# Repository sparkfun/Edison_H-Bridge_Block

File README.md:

Dual H-bridge
=====================

The Dual H-bridge give the Edison some ability to move when paired with two DC motors.  This board can drive two DC motors at voltages ranging from 2.7V-15V and currents up to 1amp.  This board is isolated from the Edison using a logic level converter.  To use this board external power for the motors will be required.  Power for the motors is supplied on the headers labled "VIN" and "GND"

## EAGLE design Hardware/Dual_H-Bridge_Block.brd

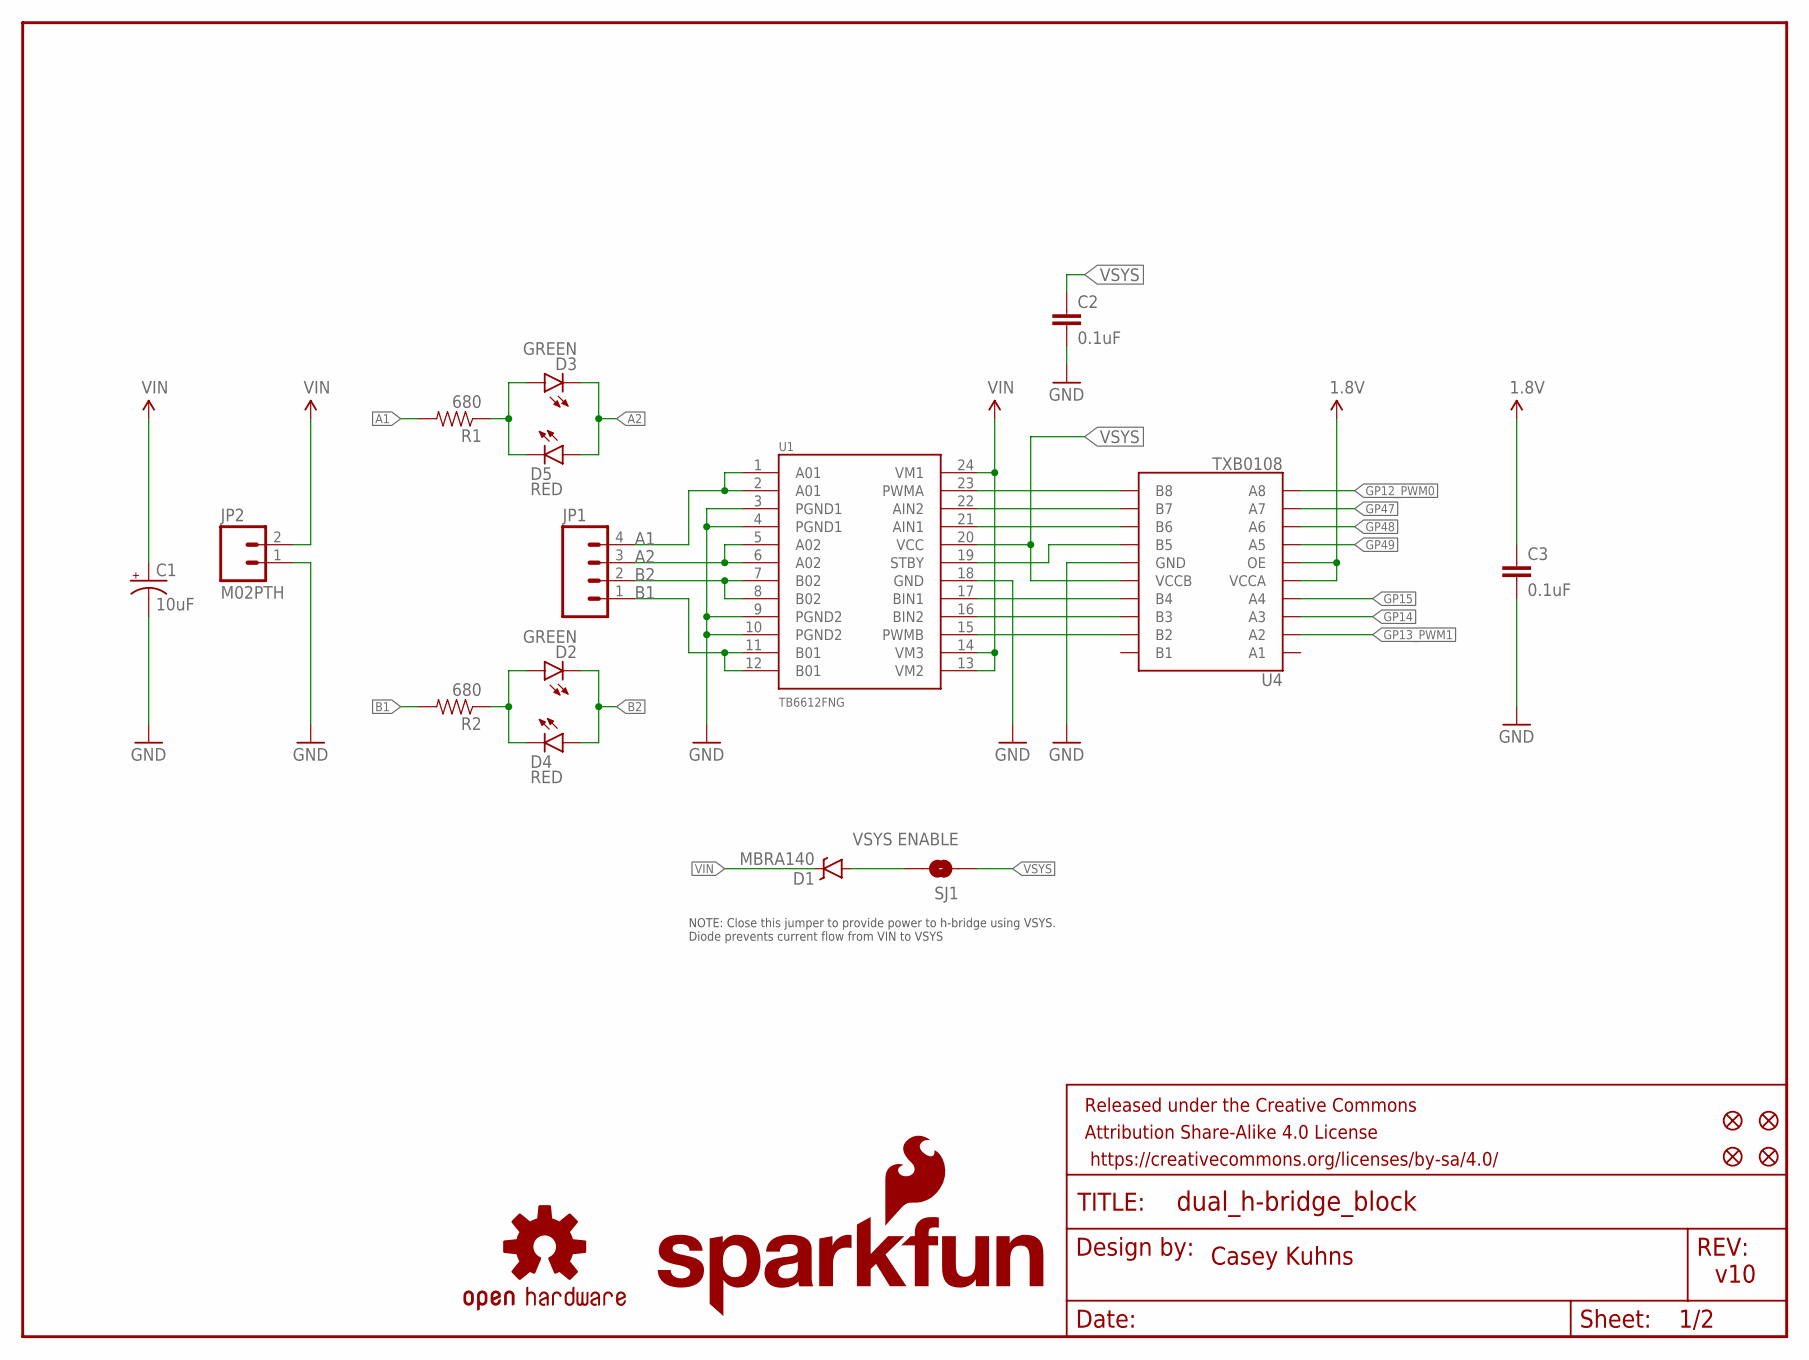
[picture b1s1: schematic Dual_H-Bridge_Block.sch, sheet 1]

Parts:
C1: 10uF; EIA3216
C2, C3: 0.1uF; 0603-CAP
D1: MBRA140; SMA-DIODE
D2, D3: GREEN; LED-0603
D4, D5: RED; LED-0603
FID1, FID2, FID3, FID4: FIDUCIAL1X2; FIDUCIAL-1X2
FRAME1: FRAME-LETTER; CREATIVE_COMMONS
JP1: M04PTH; 1X04
JP2: M02PTH; 1X02
LOGO1: OSHW-LOGOS; OSHW-LOGO-S
LOGO4: SFE_LOGO_NAME_FLAME.1_INCH; SFE_LOGO_NAME_FLAME_.1
R1, R2: 680; 0603-RES
SJ1: VSYS ENABLE; PAD-JUMPER-2-NO_YES_SILK
U1: TB6612FNG; SSOP24
U4: TXB0108; UFDFN-20

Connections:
1.8V: C3.1, U4.5 (VCCA), U4.6 (OE); also elsewhere on the board
A1: JP1.4, R1.2, U1.1 (A01), U1.2 (A01)
A2: D3.C, D5.A, JP1.3, U1.5 (A02), U1.6 (A02)
B1: JP1.1, R2.2, U1.11 (B01), U1.12 (B01)
B2: D2.C, D4.A, JP1.2, U1.7 (B02), U1.8 (B02)
GND: C1.C (-), C2.2, C3.2, JP2.1, U1.3 (PGND1), U1.4 (PGND1), U1.9 (PGND2), U1.10 (PGND2), U1.18 (GND), U4.15 (GND); also elsewhere on the board
GP12_PWM0: U4.10 (A8); also elsewhere on the board
GP13_PWM1: U4.2 (A2); also elsewhere on the board
GP14: U4.3 (A3); also elsewhere on the board
GP15: U4.4 (A4); also elsewhere on the board
GP47: U4.9 (A7); also elsewhere on the board
GP48: U4.8 (A6); also elsewhere on the board
GP49: U4.7 (A5); also elsewhere on the board
unnamed: D1.A, SJ1.2
unnamed: D2.A, D4.C, R2.1
unnamed: U1.15 (PWMB), U4.19 (B2)
unnamed: U1.23 (PWMA), U4.11 (B8)
unnamed: D3.A, D5.C, R1.1
unnamed: U1.19 (STBY), U4.14 (B5)
unnamed: U1.17 (BIN1), U4.17 (B4)
unnamed: U1.16 (BIN2), U4.18 (B3)
unnamed: U1.21 (AIN1), U4.13 (B6)
unnamed: U1.22 (AIN2), U4.12 (B7)
VIN: C1.A (+), D1.C, JP2.2, U1.13 (VM2), U1.14 (VM3), U1.24 (VM1)
VSYS: C2.1, SJ1.1, U1.20 (VCC), U4.16 (VCCB); also elsewhere on the board

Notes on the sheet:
v10
Casey Kuhns
NOTE: Close this jumper to provide power to h-bridge using VSYS. Diode prevents current flow from VIN to VSYS

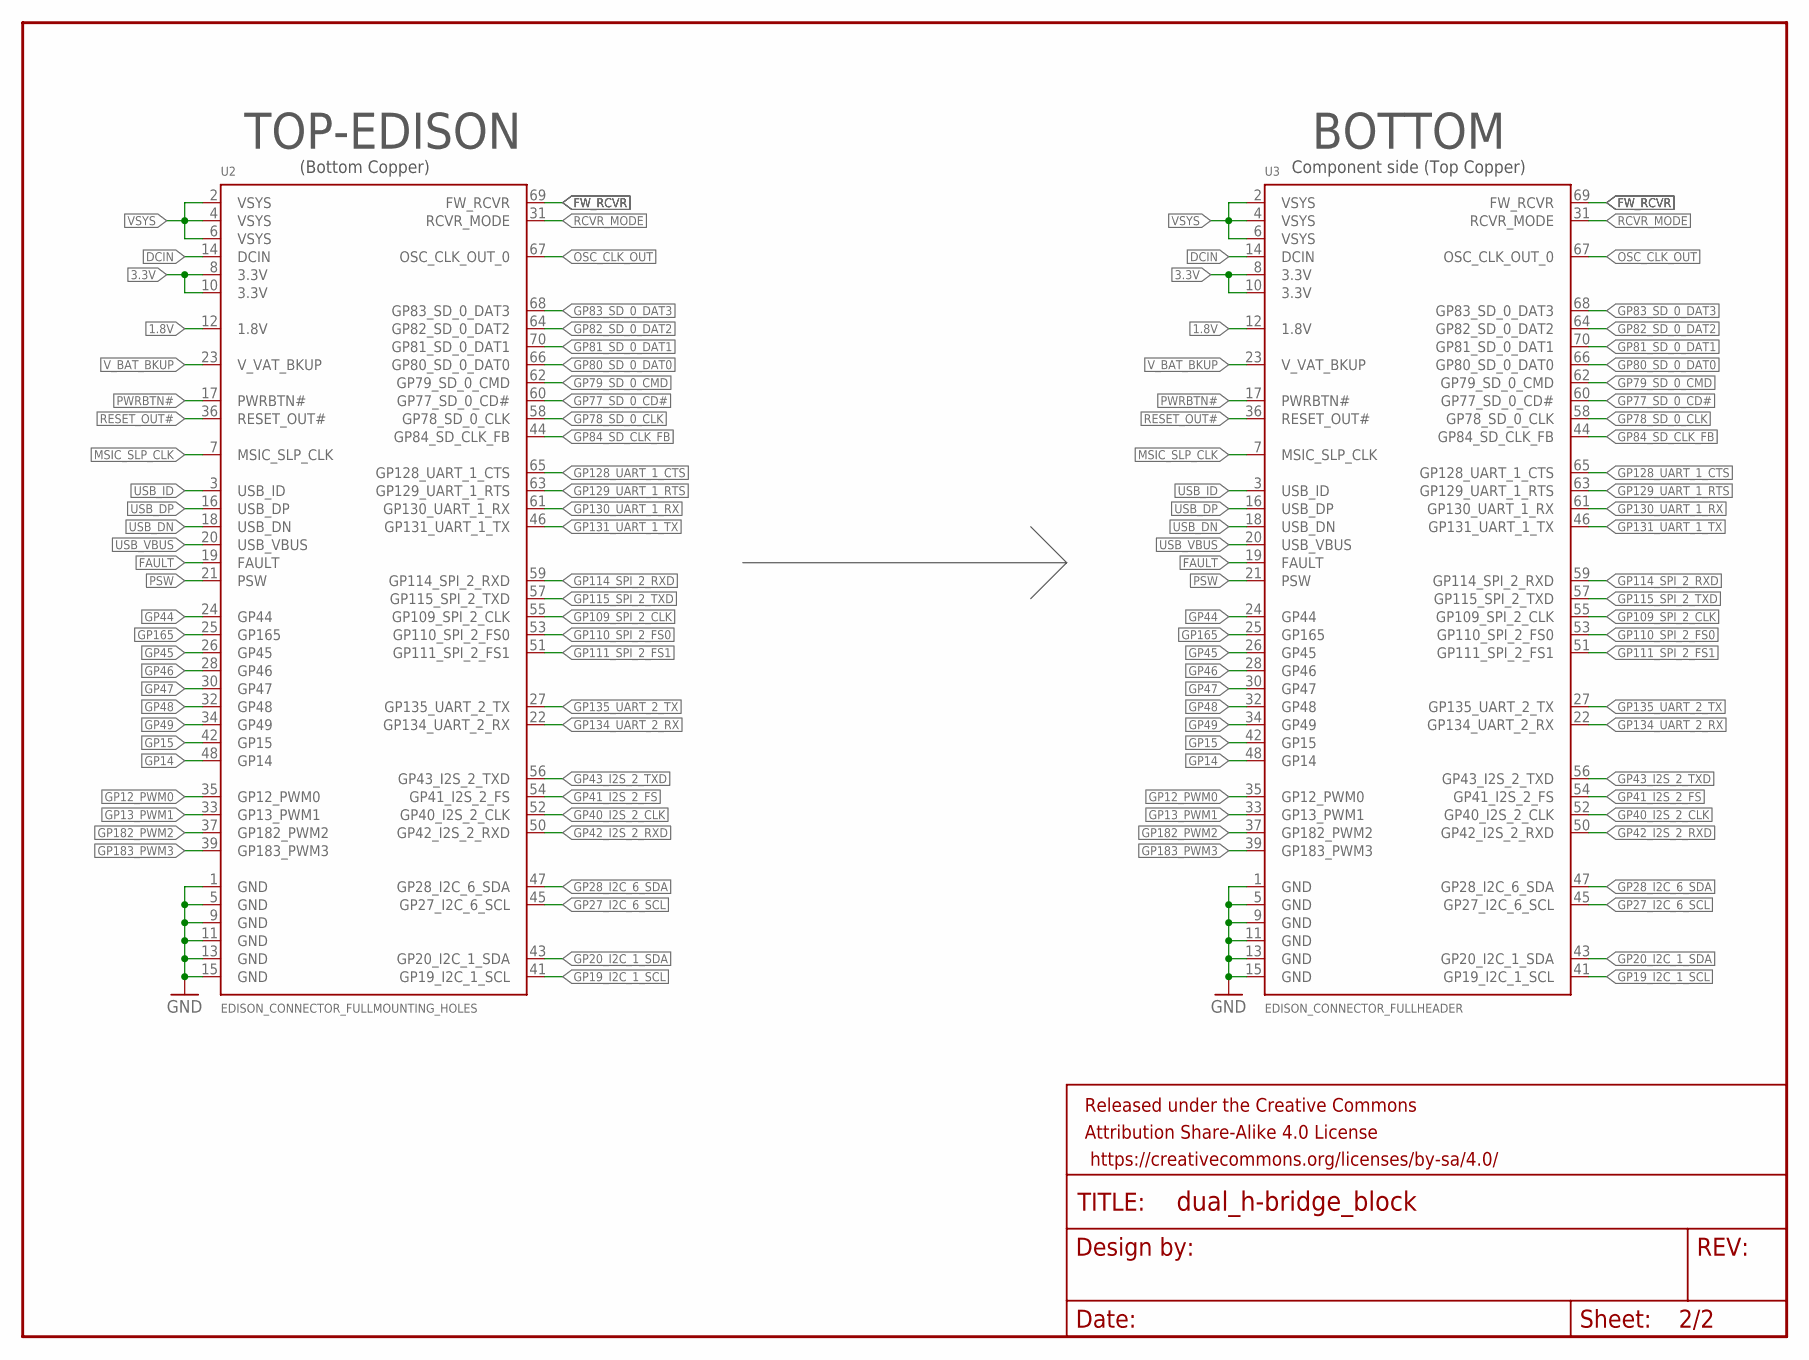
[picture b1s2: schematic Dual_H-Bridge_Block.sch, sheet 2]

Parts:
FRAME2: FRAME-LETTER; CREATIVE_COMMONS
U2: EDISON_CONNECTOR_FULLMOUNTING_HOLES; EDISON_DAUGHTER
U3: EDISON_CONNECTOR_FULLHEADER; DF40C-70DP-0.4(51)

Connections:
1.8V: U2.12 (1.8V), U3.12 (1.8V); also elsewhere on the board
3.3V: U2.8 (3.3V), U2.10 (3.3V), U3.8 (3.3V), U3.10 (3.3V)
DCIN: U2.14 (DCIN), U3.14 (DCIN)
FAULT: U2.19 (FAULT), U3.19 (FAULT)
FW_RCVR: U2.69 (FW_RCVR), U3.69 (FW_RCVR)
GND: U2.1 (GND), U2.5 (GND), U2.9 (GND), U2.11 (GND), U2.13 (GND), U2.15 (GND), U3.1 (GND), U3.5 (GND), U3.9 (GND), U3.11 (GND), U3.13 (GND), U3.15 (GND); also elsewhere on the board
GP12_PWM0: U2.35 (GP12_PWM0), U3.35 (GP12_PWM0); also elsewhere on the board
GP13_PWM1: U2.33 (GP13_PWM1), U3.33 (GP13_PWM1); also elsewhere on the board
GP14: U2.48 (GP14), U3.48 (GP14); also elsewhere on the board
GP15: U2.42 (GP15), U3.42 (GP15); also elsewhere on the board
GP19_I2C_1_SCL: U2.41 (GP19_I2C_1_SCL), U3.41 (GP19_I2C_1_SCL)
GP20_I2C_1_SDA: U2.43 (GP20_I2C_1_SDA), U3.43 (GP20_I2C_1_SDA)
GP27_I2C_6_SCL: U2.45 (GP27_I2C_6_SCL), U3.45 (GP27_I2C_6_SCL)
GP28_I2C_6_SDA: U2.47 (GP28_I2C_6_SDA), U3.47 (GP28_I2C_6_SDA)
GP40_I2S_2_CLK: U2.52 (GP40_I2S_2_CLK), U3.52 (GP40_I2S_2_CLK)
GP41_I2S_2_FS: U2.54 (GP41_I2S_2_FS), U3.54 (GP41_I2S_2_FS)
GP42_I2S_2_RXD: U2.50 (GP42_I2S_2_RXD), U3.50 (GP42_I2S_2_RXD)
GP43_I2S_2_TXD: U2.56 (GP43_I2S_2_TXD), U3.56 (GP43_I2S_2_TXD)
GP44: U2.24 (GP44), U3.24 (GP44)
GP45: U2.26 (GP45), U3.26 (GP45)
GP46: U2.28 (GP46), U3.28 (GP46)
GP47: U2.30 (GP47), U3.30 (GP47); also elsewhere on the board
GP48: U2.32 (GP48), U3.32 (GP48); also elsewhere on the board
GP49: U2.34 (GP49), U3.34 (GP49); also elsewhere on the board
GP77_SD_0_CD#: U2.60 (GP77_SD_0_CD#), U3.60 (GP77_SD_0_CD#)
GP78_SD_0_CLK: U2.58 (GP78_SD_0_CLK), U3.58 (GP78_SD_0_CLK)
GP79_SD_0_CMD: U2.62 (GP79_SD_0_CMD), U3.62 (GP79_SD_0_CMD)
GP80_SD_0_DAT0: U2.66 (GP80_SD_0_DAT0), U3.66 (GP80_SD_0_DAT0)
GP81_SD_0_DAT1: U2.70 (GP81_SD_0_DAT1), U3.70 (GP81_SD_0_DAT1)
GP82_SD_0_DAT2: U2.64 (GP82_SD_0_DAT2), U3.64 (GP82_SD_0_DAT2)
GP83_SD_0_DAT3: U2.68 (GP83_SD_0_DAT3), U3.68 (GP83_SD_0_DAT3)
GP84_SD_CLK_FB: U2.44 (GP84_SD_CLK_FB), U3.44 (GP84_SD_CLK_FB)
GP109_SPI_2_CLK: U2.55 (GP109_SPI_2_CLK), U3.55 (GP109_SPI_2_CLK)
GP110_SPI_2_FS0: U2.53 (GP110_SPI_2_FS0), U3.53 (GP110_SPI_2_FS0)
GP111_SPI_2_FS1: U2.51 (GP111_SPI_2_FS1), U3.51 (GP111_SPI_2_FS1)
GP114_SPI_2_RXD: U2.59 (GP114_SPI_2_RXD), U3.59 (GP114_SPI_2_RXD)
GP115_SPI_2_TXD: U2.57 (GP115_SPI_2_TXD), U3.57 (GP115_SPI_2_TXD)
GP128_UART_1_CTS: U2.65 (GP128_UART_1_CTS), U3.65 (GP128_UART_1_CTS)
GP129_UART_1_RTS: U2.63 (GP129_UART_1_RTS), U3.63 (GP129_UART_1_RTS)
GP130_UART_1_RX: U2.61 (GP130_UART_1_RX), U3.61 (GP130_UART_1_RX)
GP131_UART_1_TX: U2.46 (GP131_UART_1_TX), U3.46 (GP131_UART_1_TX)
GP134_UART_2_RX: U2.22 (GP134_UART_2_RX), U3.22 (GP134_UART_2_RX)
GP135_UART_2_TX: U2.27 (GP135_UART_2_TX), U3.27 (GP135_UART_2_TX)
GP165: U2.25 (GP165), U3.25 (GP165)
GP182_PWM2: U2.37 (GP182_PWM2), U3.37 (GP182_PWM2)
GP183_PWM3: U2.39 (GP183_PWM3), U3.39 (GP183_PWM3)
MSIC_SLP_CLK: U2.7 (MSIC_SLP_CLK), U3.7 (MSIC_SLP_CLK)
OSC_CLK_OUT: U2.67 (OSC_CLK_OUT_0), U3.67 (OSC_CLK_OUT_0)
PSW: U2.21 (PSW), U3.21 (PSW)
PWRBTN#: U2.17 (PWRBTN#), U3.17 (PWRBTN#)
RCVR_MODE: U2.31 (RCVR_MODE), U3.31 (RCVR_MODE)
RESET_OUT#: U2.36 (RESET_OUT#), U3.36 (RESET_OUT#)
USB_DN: U2.18 (USB_DN), U3.18 (USB_DN)
USB_DP: U2.16 (USB_DP), U3.16 (USB_DP)
USB_ID: U2.3 (USB_ID), U3.3 (USB_ID)
USB_VBUS: U2.20 (USB_VBUS), U3.20 (USB_VBUS)
VSYS: U2.2 (VSYS), U2.4 (VSYS), U2.6 (VSYS), U3.2 (VSYS), U3.4 (VSYS), U3.6 (VSYS); also elsewhere on the board
V_BAT_BKUP: U2.23 (V_VAT_BKUP), U3.23 (V_VAT_BKUP)

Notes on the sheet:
TOP-EDISON
BOTTOM
Component side (Top Copper)
(Bottom Copper)

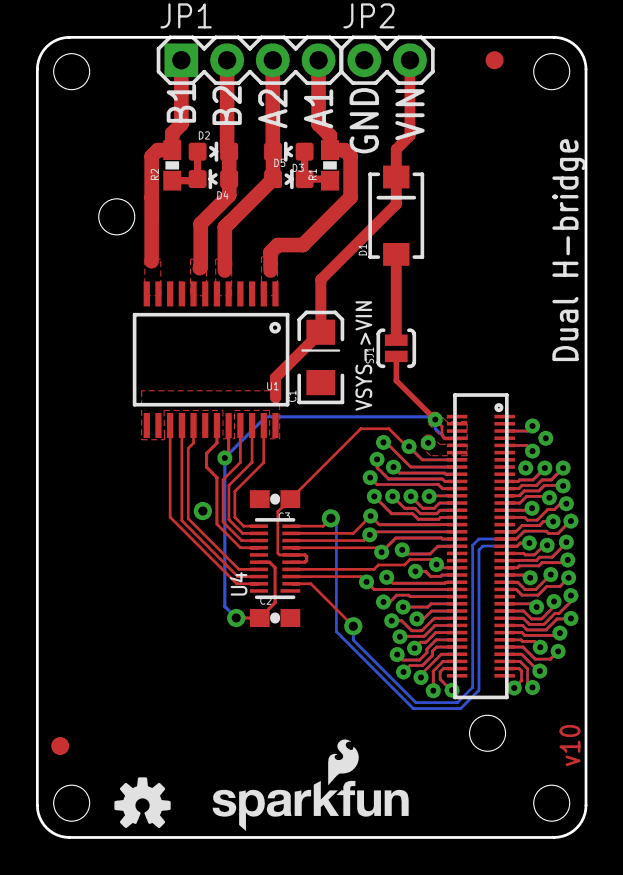
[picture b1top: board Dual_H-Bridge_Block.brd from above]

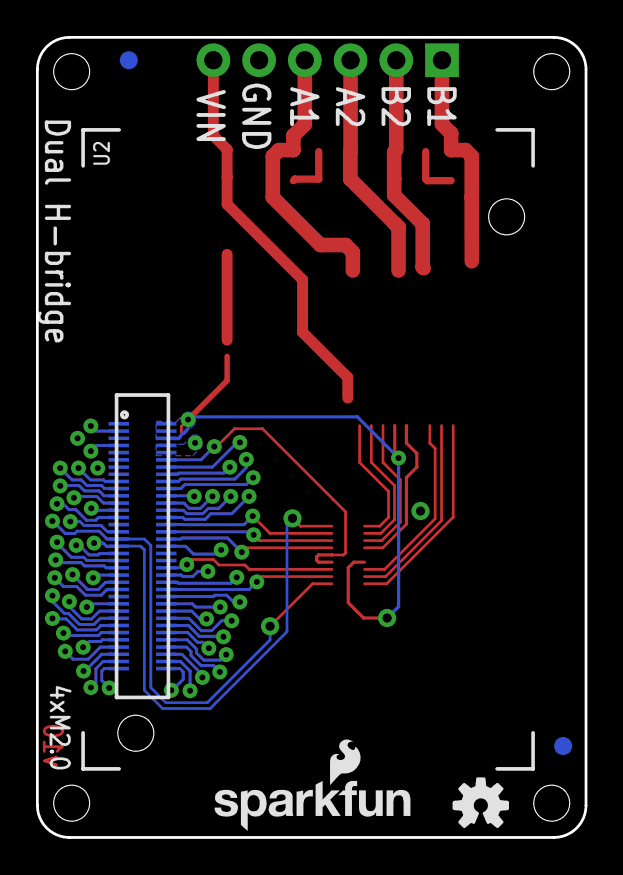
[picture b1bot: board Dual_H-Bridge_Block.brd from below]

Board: 2 copper layers, 30.5 x 44.5 mm, 27 parts (6 on the bottom side), 73 nets.

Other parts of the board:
LOGO2: OSHW-LOGOS; OSHW-LOGO-S
LOGO3: SFE_LOGO_NAME_FLAME.1_INCH; SFE_LOGO_NAME_FLAME_.1

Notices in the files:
parts and their libraries:
SparkFun-Aesthetics: Licensing: Creative Commons ShareAlike 4.0 International - https://creativecommons.org/licenses/by-sa/4.0
SparkFun-Aesthetics: Released under the Creative Commons Attribution Share-Alike 4.0 License
SparkFun-Aesthetics: https://creativecommons.org/licenses/by-sa/4.0
